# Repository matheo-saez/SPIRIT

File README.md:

<p align="center">
    
    <br>

</p>

Open source smartphone, from available components. Prioritizing user experience, performance, control, repairability, innovation and privacy.
Contribution and feedback are very welcome! [Contribution Guide](https://github.com/V3lectronics/SPIRIT/blob/main/CONTRIBUTING.md).
(Currently in the development phase, progress documented here and on the V Electronics [YT channel](https://www.youtube.com/@V_Electronics)).

> [!WARNING]
> For imformation about the project please refer to the **[wiki](https://github.com/V3lectronics/SPIRIT/wiki)**, the contents below may be outdated.
> Soon all information will be moved to the wiki!

# Contents
1. [General Specifications](https://github.com/barbarjan/SPIRIT#general-specifications)
2. [Hardware And Electronics](https://github.com/barbarjan/SPIRIT#hardware-and-electronics)
3. [Software And Operating System](https://github.com/barbarjan/SPIRIT#software-and-operating-system)
4. [DIY Build Guide](https://github.com/barbarjan/SPIRIT#diy-build-guide)
5. [Parts List](https://github.com/barbarjan/SPIRIT#parts-list)
6. [Cost](https://github.com/barbarjan/SPIRIT#cost)
7. [Ethical And Environmental Concerns](https://github.com/barbarjan/SPIRIT#ethical-and-environmental-concerns)
8. [Compliance And Legality](https://github.com/barbarjan/SPIRIT#compliance-and-legality)
9. [Resources](https://github.com/barbarjan/SPIRIT#resources)

---

Early screenshots:

# General Specifications

#### RAM

- 2GB / 4GB / 8GB / 16GB LPDDR4

#### CPU

- Broadcom BCM2712 64-bit 2.4 GHz, 4 cores with 4 threads

#### Storage

- 16GB, 32GB, or 64GB eMMC

#### Connectivity (IO)

- 1 x USB C 3.2 (Iphone 16 is USB 2.0 just throwing that out there)
- 2.4 GHz, 5.0 GHz WiFi
- Bluetooth 5
- GSM
- GPS

#### Screen

- 5.5" Capacitive Touch TFT Display
- resolution: 720x1280 pixels

#### Battery

_will probably change soon because of component availability_
- Capacity: 2.05Ah
- Type: Lithium Polymer
- Voltage: 3.7 V
- Dimensions: 84.5mm x 47.5mm x 6.0mm (3.33" 1.87" 0.24")
- The battery can be easily swapped for a fully charged one to effectively get back to 100%
almost instantly.

#### Dimensions

Chassis: ?

PCB: 80mm x 150mm

Total: thickness is ~12.3mm (excluding camera module lens sticking out)

Main components that contribute thickness:

| Component      | Thickness |
|----------------|-----------|
| Chassis        | 1 mm      |
| PCB            | 1.4 mm    |
| Battery        | 6 mm      |
| Screen         | 3.9 mm    |

#### Camera

SPIRIT is compatible with [Arducam](https://www.arducam.com/) cameras e.g. the [64 MP Hawkeye](https://www.arducam.com/64mp-ultra-high-res-camera-raspberry-pi/) or the more affordable [16 MP Autofocus](https://www.arducam.com/16mp-autofocus-camera-for-raspberry-pi/).

The camera module can be completely powered off by the user using a physical switch.

Below are the stats for the Hawkeye:

| Name    | Sensor Resolution  | Zoom | Field Of View |
|---------|-----------------|-----|---------------|
|Pi Hawk-eye| 64MP (9152 x 6944 pixels) |  10x (digital) | 84 degrees |

Sensor: 1/1.7" stacked CMOS image sensor, 0.8 μm pixel size Lens: f/1.8 aperture, 8 cm–∞ focal range, motorised focusing Max Resolution: 9152×6944 stills; 1080p 30 fps video

For more details see the [product page](https://www.arducam.com/64mp-ultra-high-res-camera-raspberry-pi/)

*(For now there is only one camera for simplicity and cost reduction)*

# Hardware And Electronics

### Raspberry Pi Compute Module 5

"The power of Raspberry Pi 5 in a compact form factor for deeply embedded applications" [(CM5 website)](https://www.raspberrypi.com/products/compute-module-5/?variant=cm5-104032).

By default SPIRIT uses the 4GB RAM, 64GB eMMC version of the CM. It is possible to use a different CM5 variant (for example to increase the RAM to 8GB).

### EDA

For schematics, PCB layout etc. the newest major release of KiCad is used.

All EDA files are available through this repository (see the 'EDA-kicad' folder). The best way to view them is to clone the repo to your machine and use KiCad to open the project file 'cm5-carrier.kicad_pro'.

### Carrier PCB

Custom carrier board (motherboard) that interfaces between the Compute Module and the rest of the electronics.

This is the only custom electronic component in this project.

### Touchscreen

Capacitive LCD Display TFT MIPI 
Dimensions: 5.5" (139.70mm) 1280px x 720px

### Replaceable Battery

Can be completely disconnected by the user using a physical switch.

The battery is mounted such that it can be easily uninstalled for replacing or privacy reasons. The user is free to swap the battery for any compatible model.
It is also possible to run the phone without a battery, or using an external one
if you attach long enough wires.

An added benefit is that the user can easily replace an empty battery for a charged one - effectively eliminating the need to wait for the phone to charge. An external battery charger can also be used for unmounted batteries.

### GSM, GPS Module

EC25VFA-512-STD

Can be completely powered off by the user using a physical switch.
Cellular, Navigation BeiDou, EDGE, Galileo, GLONASS, GPS, GNSS, LTE Transceiver Module 1.561GHz, 1.575GHz, 1.602GHz

### Speakers

2 x CMR-15062S-67

The speaker system consists of a pair of speakers mounted symmetrically facing upwards.

### Biometric Module

100018754

The fingerprint scanner is located on the back of the phone and has a sensing
area of 8x8mm. It is rated for 10 million finger placements and can store up to
50 templates.

False acceptance rate: 1/500k (per finger)
False rejection rate: 1.4-3.5 %

### Headphone Jack

This phone has a TRRS headphone jack. This way the user can decide between wireless or wired.

### Microphone

SPH0645LM4H-B

Can be completely powered off by the user using a physical switch.
Omnidirectional with a theorethical frequency range 20 Hz - 10 kHz.
Sensitivity: -26dB ±3dB @ 94dB SPL.
Digital output (I2S)

### Buttons

The power, volume and programmable buttons are identical rectangular, tactile switches with a life
expectancy of 30k cycles.

The Programmable Button's function can be customized by the user. For example, it can be used for quick launching an app, instantly dialing a saved contact, toggling sound settings (silent, vibrate, sound) etc. The list of potential use cases is very long. One of them could be enabling small children or elderly people to instantly call for example a parent, or supervisor in case of emergency. Another could be to immediately launch the camera app to quickly capture a moment.

### Privacy Switches

SPIRIT has 4 physical switches that cut off the power lines to specific modules
ensuring they are 100% inactive and not drawing power. Notice, you can also
completely disconnect the battery. Needless to say, this is a very useful
feature for people who want to have direct control over the hardware and want to
protect their privacy without having to trust software.

| Switch Number | Module |
|----------------|-----------|
| 1| Microphone|
| 2|GPS/GSM EC25 chip |
| 3|Camera |
| 4|Battery |

### Flashlight

LXML-PWC1-0100

1W 3V white, cool LED.

Toggling on/off can be binded to the programmable button.

# Software And Operating System

Once the hardware platform is functional it will be time to test various operating
systems as well as explore the possibility of developing one based on Debian.

List of operating systems to test/research:

| Name           | Website |
|----------------|-----------|
| Ubuntu Touch   | https://ubuntu-touch.io/     |
| Lineage        | https://lineageos.org/    |
| Graphene       | https://grapheneos.org/features      |
| Android        | https://www.android.com/      |

Additionally, The Yocto Project has been suggested (not an OS) https://www.yoctoproject.org/

# DIY Build Guide

Link to build guide/tutorial: COMING SOON!!!

# Parts List

The list is incomplete and old, it will be updated as soon as we have built the 1st prototype

To get the most up-to-date parts list please look
at the BOM. Certain components such as the camera or the compute module can be swapped for a different
model - the presented setup is just a suggestion.

<details>
      <summary>Click here to show/hide</summary>

| Amount | Name | Unit Price (USD)| Digikey Link |
|--------|------|---------------|--------------|
|1|RPi CM4 |65|https://www.digikey.pl/en/products/detail/raspberry-pi/SC0686/13530938?s=N4IgjCBcoLQCxVAYygMwIYBsDOBTANCAPZQDaIAHAJwAMVA7CALoC%2BLhATGSBwGxwUYAZQDCNZiyA|
|1| Carrier PCB|?|N/A|
|1| Touch screen|96,99|https://www.digikey.pl/en/products/detail/nxp-usa-inc/RK055HDMIPI4MA0/16274141 |
|1| Main Camera|66|https://www.digikey.com/en/products/detail/sparkfun-electronics/SEN-21276/21443092 |
|1| Battery|9,85|https://www.digikey.pl/en/products/detail/jauch-quartz/LP504783JU-PCM-2-WIRES-70MM/13540155|
|1| ??? BMS chip | | |
|1| 21 pin FFC connector|2.76|https://www.digikey.ca/en/products/detail/hirose-electric-co-ltd/FH72-31S-0-3SHW/13553267|
|1| 22 pin FFC connector|2,21|https://www.digikey.pl/en/products/detail/hirose-electric-co-ltd/FH12-22S-0-5SH-55/1110321|
|1| 10 pin FFC connector|0,20|https://www.digikey.pl/en/products/detail/te-connectivity-amp-connectors/1-2328702-0/9565577|
|1| Flashlight LED|3,03|https://www.digikey.pl/en/products/detail/lumileds/LXML-PWC1-0100/3961144|
|1| 35mm Jack|0.97|https://www.digikey.com/en/products/detail/same-sky-formerly-cui-devices/SJ2-3574A-SMT-TR/6619530|
|2| Speaker|2,53|https://www.digikey.pl/en/products/detail/cui-devices/CMR-15062S-67/9561156|
|1| Microphone|1,95|https://www.digikey.pl/en/products/detail/knowles/SPH0645LM4H-B/5332440|
|1| USB C 2.0 Connector|0,81|https://www.digikey.com/en/products/detail/gct/USB4105-GF-A/11198441|
|?| Overvoltage protector|0,43|https://www.digikey.pl/en/products/detail/littelfuse-inc/SMBJ5-0A/285950|
|1| Fingerprint Card|29|https://www.digikey.pl/en/products/detail/fingerprint-cards-ab/100018754/11480144?s=N4IgjCBcpgnAHLKoDGUBmBDANgZwKYA0IA9lANogAMIAugL7EC0ATMiGpAC4BOArkVIUQAVjqMQTAGztOvAcTKRKAZhDE2DCW2Uh0ASwB2Ac3w8ADjyNdxQA|
|1| GPS Module|7,25|https://www.digikey.pl/en/products/detail/yic/YIC31009EBGG/16499057|
|1| GSM Module|||
|1| Vibration Motor|1,71|https://www.digikey.pl/en/products/detail/pui-audio-inc/HD-EMB1205-3-SC-R/16522073|
|1| Small LED|||
|1| Thermistor|0,10|https://www.digikey.pl/en/products/detail/panasonic-electronic-components/ERT-JZEG103FA/9646736|
|1| DAC for audio output||
|1| Jumper female nRPI_BOOT||
|1| Jumper female GND||
|?| Header pins||
|?| M1.6 stainless screws||
|?| M? RPi size stainless screws||
|?| M? Arducam size stainless screws||
|?| M? RPi size stainless tandoffs||

</details>

# Cost

The total assembly cost of the device is unknown

# Ethical And Environmental Concerns

SPIRIT phones avoid components produced in unfair or harmful ways, as well as
containing conflict minerals if possible.

TODO
Here are ethical details for each major component:

-Chassis
-CM5
-Battery
-Screen
-Chassis
-Speakers

The goal is to be 100% ethically and environmentally "clean" as soon as possible, however that is
a hard task and presents multiple enginnering challenges.

TODO
?RoHS complicance

# Compliance And Legality

TODO research

### EU

Ecodesign Regulation 2023/1670

?EMI norms

?RoHS

?REACH

?WEEE

### N America
?

### S America
?

### Asia
?

### Africa
?

### Australia
?

# Resources

- [Rpi CM5 datasheet](https://datasheets.raspberrypi.com/cm5/cm5-datasheet.pdf)
- [Rpi CM4 pinout from datasheet](https://datasheets.raspberrypi.com/cm4/cm4-datasheet.pdf#page=18)
- [Rpi CM5 and CM 4 very useful interactive pinout](https://atctwo.net/projects/pinout/index.html)

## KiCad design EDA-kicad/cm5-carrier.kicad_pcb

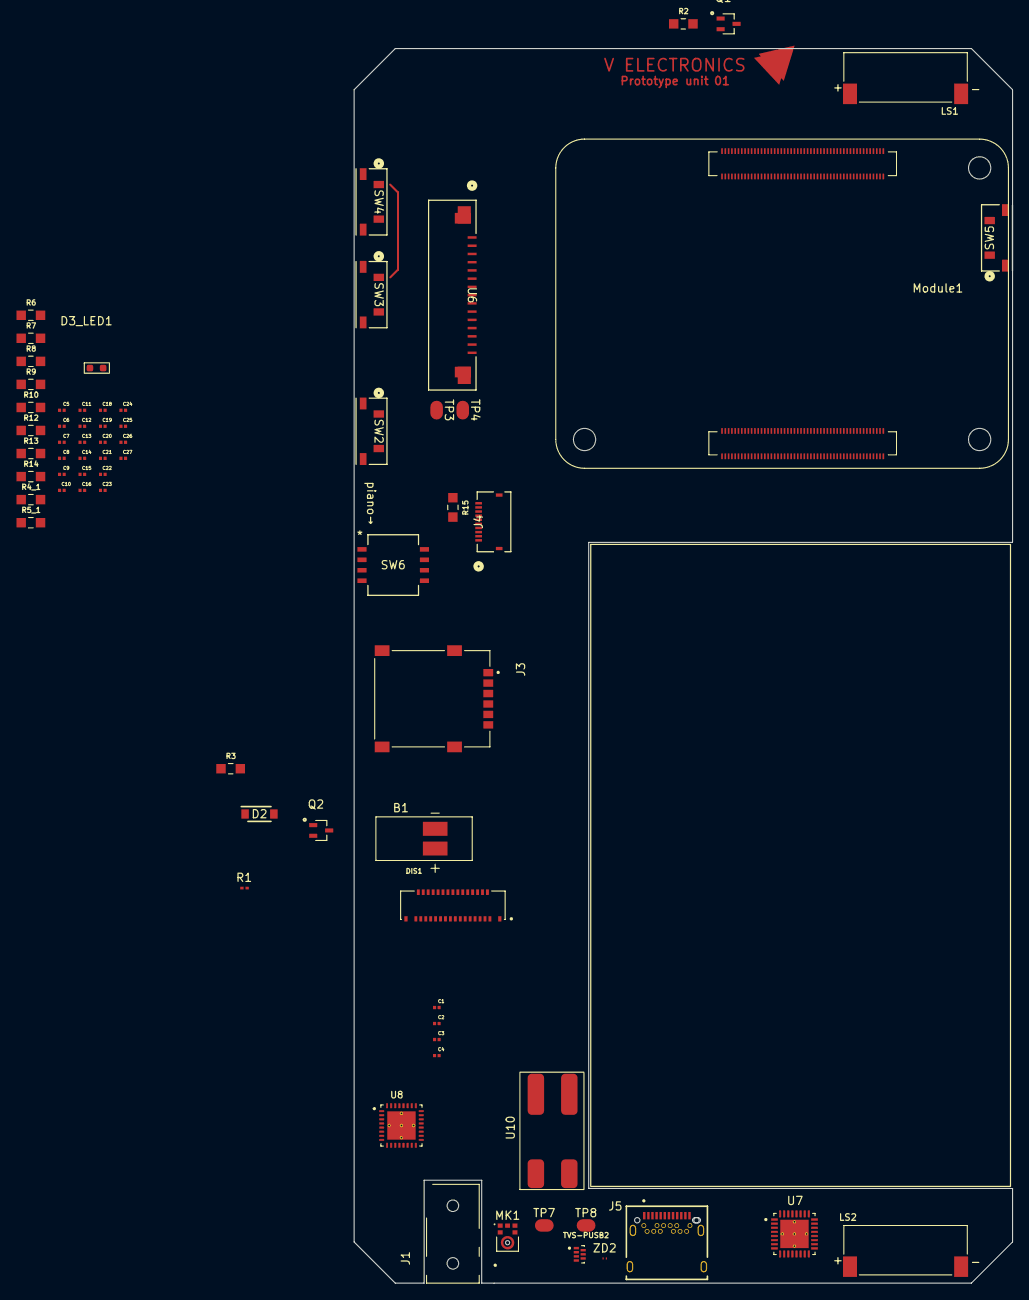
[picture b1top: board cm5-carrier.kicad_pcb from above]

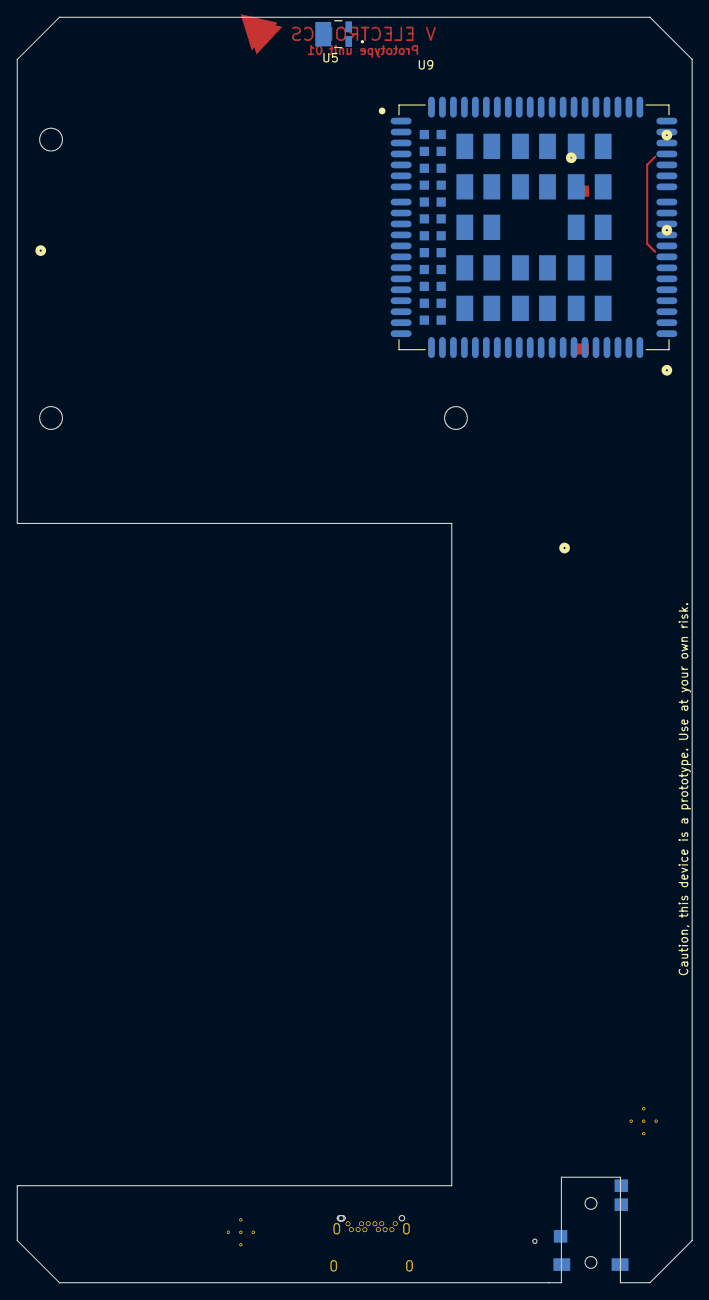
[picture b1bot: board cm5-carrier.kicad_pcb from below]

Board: 2 copper layers, 80.0 x 150.0 mm, 72 parts (2 on the bottom side), 63 nets.

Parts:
B1: VIBR; VIBRATION-PUI_HD-EMB1205-3-SC-R
BAT2: battery_37V3500mAhLP685077JU
C1, C2, C3, C4: 0.33 µF coupling cap; USBC_capacitor_CAPC0603X33N
C5, C11, C21, C24, C27: 0.1μF; USBC_capacitor_CAPC0603X33N
C6, C7, C8, C9, C10, C12, C13, C14, C15, C16, C22, C23: 10μF; USBC_capacitor_CAPC0603X33N
C18, C19: 47nF; USBC_capacitor_CAPC0603X33N
C20: 4.7μF; USBC_capacitor_CAPC0603X33N
C25, C26: 2.2μF; USBC_capacitor_CAPC0603X33N
D2: 1N4007W-T; flyback-diode-SODFL3818X130N
D3_LED1: LED-INDICATOR
DIS1: FH72-31S-0.3SHW; HRS_FH72-31S-0.3SHW
J1: SJ2-35894B-SMT-TR; 35mmJACK-CUI_SJ2-35894B-SMT-TR
J3: SIM-G85D1160022HHR; SIM-AMPHENOL_G85D1160022HHR
J4: FINGER; 10PIN
J5: USBC-3-2-fix-USB4056-03-A_REVA2; USBC-3-2-fix-GCT_USB4056-03-A_REVA2
LS1, LS2: CMR-15062S-67; SPEAKER_CMR-15062S-67
MK1: microphone; microphone_SPH0645LM4H-B
Module1: ComputeModule5-CM5; Raspberry-Pi-5-Compute-Module
Q1, Q2: gpio-driver-transistor-fix-SOT65P210X110-3N
R1: thermistor; thermistor-NTC0201Z_P63XP33_PAN
R2, R3: 1K-05W-0805-RES_ERJP06J102V
R4_1: 6.04k; 1K-05W-0805-RES_ERJP06J102V
R5_1: 100k; 1K-05W-0805-RES_ERJP06J102V
R6: 5.24k; 1K-05W-0805-RES_ERJP06J102V
R7: 30.31k; 1K-05W-0805-RES_ERJP06J102V
R8: 10k; 1K-05W-0805-RES_ERJP06J102V
R9: 100; 1K-05W-0805-RES_ERJP06J102V
R10, R12: R; 1K-05W-0805-RES_ERJP06J102V
R13, R14: 2; 1K-05W-0805-RES_ERJP06J102V
R15: 270K-05W-0805-RES_ERJP06J102V; 1K-05W-0805-RES_ERJP06J102V
SW2: PROG; buttonSW_TL3330_EWI
SW3: VOL-; buttonSW_TL3330_EWI
SW4: VOL+; buttonSW_TL3330_EWI
SW5: POW; buttonSW_TL3330_EWI
SW6: CHP-041B; pianoCHP-041B_NDC
TP3, TP4, TP7, TP8: test-pad-1
TVS-PUSB2: TVS-array-IC_PUSB3AB6Z
U5: Flash-LED-Lumiled; LUMILED-DIODFN449X305X210-3N
U6: FPC15pin-1mm-pitch-F52Q-1A7H1-11015; FPC15pin-1mm-pitch-CONN_F52Q-1A7H1-11015_AMP
U7: CODEC-TLV320AIC3204IRHBR; CODEC-QFN50P500X500X100-33N
U8: DAC-TLV320DAC3100IRHBR; DAC-IC_ADS125H01IRHBT
U9: GSM-GPS-EC25VFA-512-STD; GSM-GPS-XCVR_EC25VFA-512-STD
U10: BAT-CONNECTOR-FLTS22WR00
ZD2: protection-PESD5V0C1USFYL; USB-ESD-protection-diode-PESD5V0C1USFYL-SOD962-2_DSN0603-2_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

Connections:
BAT: C15.1, C16.1
CAM-SWITCH: SW6.6, TP3.1 (A), U6.15
CAM_CK_N: Module1.127 (MIPI0_C_N), U6.8
CAM_CK_P: Module1.129 (MIPI0_C_P), U6.9
CAM_D0_N: Module1.115 (MIPI0_D0_N), U6.2
CAM_D0_P: Module1.117 (MIPI0_D0_P), U6.3
CAM_D1_N: Module1.121 (MIPI0_D1_N), U6.5
CAM_D1_P: Module1.123 (MIPI0_D1_P), U6.6
CAM_IO0: TP4.1 (A), U6.11
CC1: J5.A5 (CC1), Module1.94 (CC1)
CC2: J5.B5 (CC2), Module1.96 (CC2)
CODEC SCL: Module1.51 (GPIO15), U7.9 (SCL/~SS)
CODEC SDA: Module1.31 (GPIO12), U7.10 (SDA/MOSI)
D+: J5.A6 (DP1), J5.B6 (DP2), Module1.163 (USB3-1-D_P), TVS-PUSB2.5 (D+)
D-: J5.A7 (DN1), J5.B7 (DN2), Module1.165 (USB3-1-D_N), TVS-PUSB2.4 (D-)
DIS SCL: DIS1.27, Module1.37 (GPIO7)
DIS SDA: DIS1.26, Module1.30 (GPIO6)
DSI1_C_N: DIS1.11, Module1.187 (MIPI1_C_N)
DSI1_C_P: DIS1.12, Module1.189 (MIPI1_C_P)
DSI1_D0_N: DIS1.5, Module1.175 (MIPI1_D0_N)
DSI1_D0_P: DIS1.6, Module1.177 (MIPI1_D0_P)
DSI1_D1_N: DIS1.8, Module1.181 (MIPI1_D1_N)
DSI1_D1_P: DIS1.9, Module1.183 (MIPI1_D1_P)
DSI1_D2_N: DIS1.14, Module1.133 (MIPI0_D2_N), Module1.193 (MIPI1_D2_N)
DSI1_D2_P: DIS1.15, Module1.135 (MIPI0_D2_P), Module1.195 (MIPI1_D2_P)
GND: C5.2, C6.2, C7.2, C8.2, C9.2, C10.2, C11.2, C12.2, C13.2, C14.2, C15.2, C16.2, C20.2, C21.2, C22.2, C23.2, C24.2, C25.2, C26.2, C27.2, DIS1.1, DIS1.4, DIS1.7, DIS1.10, DIS1.13, DIS1.16, DIS1.19, DIS1.20, DIS1.31, J3.C5 (GND), J3.S1 (SHIELD_GND), J3.S2 (SHIELD_GND__1), J3.S3 (SHIELD_GND__2), J4.1, J5.A1 (GND_A), J5.A12 (GND_A__1), J5.B1 (GND_B), J5.B12 (GND_B__1), J5.S1 (SHELL_GND), J5.S2 (SHELL_GND__1), J5.S3 (SHELL_GND__2), J5.S4 (SHELL_GND__3), MK1.3 (GND), Module1.1 (GND), Module1.2 (GND), Module1.8 (GND), Module1.13 (GND), Module1.14 (GND), Module1.22 (GND), Module1.23 (GND), Module1.32 (GND), Module1.33 (GND), Module1.42 (GND), Module1.43 (GND), Module1.52 (GND), Module1.53 (GND), Module1.60 (GND), Module1.66 (GND), Module1.71 (GND), Module1.74 (GND), Module1.98 (GND), Module1.107 (GND), Module1.108 (GND), Module1.113 (GND), Module1.114 (GND), Module1.119 (GND), Module1.120 (GND), Module1.125 (GND), Module1.126 (GND), Module1.131 (GND), Module1.132 (GND), Module1.137 (GND), Module1.138 (GND), Module1.144 (GND), Module1.150 (GND), Module1.155 (GND), Module1.156 (GND), Module1.161 (GND), Module1.162 (GND), Module1.167 (GND), Module1.168 (GND), Module1.173 (GND), Module1.174 (GND), Module1.179 (GND), Module1.180 (GND), Module1.185 (GND), Module1.186 (GND), Module1.191 (GND), Module1.192 (GND), Module1.197 (GND), Module1.198 (GND), Q1.3 (S), Q2.3 (S), R4_1.1, R5_1.2, R7.2, R8.2, TVS-PUSB2.2 (GND), U6.1, U6.4, U6.10, U7.7 (IOVSS), U7.17 (AVSS), U7.28 (DVSS), U8.1 (IOVSS), U8.16 (AVSS), U8.18 (DVSS), U8.20 (SPKVSS), U8.25 (SPKVSS__1), U8.29 (HPVSS), U9.8 (GND), U9.9 (GND__1), U9.19 (GND__2), U9.22 (GND__3), U9.36 (GND__4), U9.46 (GND__5), U9.48 (GND__6), U9.50 (GND__7), U9.51 (GND__8), U9.52 (GND__9), U9.53 (GND__10), U9.54 (GND__11), U9.56 (GND__12), U9.72 (GND__13), U9.85 (GND__14), U9.86 (GND__15), U9.87 (GND__16), U9.88 (GND__17), U9.89 (GND__18), U9.90 (GND__19), U9.91 (GND__20), U9.92 (GND__21), U9.93 (GND__22), U9.94 (GND__23), U9.95 (GND__24), U9.96 (GND__25), U9.97 (GND__26), U9.98 (GND__27), U9.99 (GND__28), U9.100 (GND__29), U9.101 (GND__30), U9.102 (GND__31), U9.103 (GND__32), U9.104 (GND__33), U9.105 (GND__34), U9.106 (GND__35), U9.107 (GND__36), U9.108 (GND__37), U9.109 (GND__38), U9.110 (GND__39), U9.111 (GND__40), U9.112 (GND__41), U10.4 (OUT-), ZD2.2
GPIO2: Module1.58 (GPIO2), SW5.2
GPIO3: Module1.56 (GPIO3), SW4.2
GPIO4: Module1.54 (GPIO4), SW3.2
GPIO17: Module1.50 (GPIO17), SW2.2
GPIO22: Module1.46 (GPIO22), R2.1
GPIO27: Module1.48 (GPIO27), R3.1
MIC-SWITCH: MK1.5 (VDD), SW6.8
unnamed: C25.1, R13.1
unnamed: C26.1, R14.1
unnamed: J4.8, R15.2
unnamed: C1.1, Module1.157 (USB3-1-RX_N)
unnamed: C2.1, Module1.159 (USB3-1-RX_P)
unnamed: C3.1, Module1.169 (USB3-1-TX_N)
unnamed: C4.1, Module1.171 (USB3-1-TX_P)
unnamed: Q1.2 (D), U5.1 (-)
unnamed: Q1.1 (G), R2.2
unnamed: B1.N, D2.2, Q2.2 (D)
unnamed: Q2.1 (G), R3.2
unnamed: C11.1, C12.1, C13.1, C14.1
unnamed: R6.2, R7.1, R8.1
OUT +: R9.2, U10.3 (OUT+)
REGN: C18.2, C19.1, C20.1, R6.1
RX1+: C2.2, J5.A11 (SSRXP2), J5.B11 (SSRXP1), TVS-PUSB2.7 (RX+)
RX1-: C1.2, J5.A10 (SSRXN2), J5.B10 (SSRXN1), TVS-PUSB2.6 (Rx-)
SPI0_CLK: J4.2, Module1.38 (GPIO11)
SPI0_CS: J4.5, Module1.39 (GPIO8)
SPI0_MISO: J4.3, Module1.40 (GPIO9)
SPI0_MOSI: J4.4, Module1.44 (GPIO10)
SPI0_RDY: J4.6, Module1.34 (GPIO5)
SYS: C5.1, C6.1, C7.1, C8.1, C9.1, C10.1
TX1+: C4.2, J5.A2 (SSTXP1), J5.B2 (SSTXP2), TVS-PUSB2.3 (Tx+)
TX1-: C3.2, J5.A3 (SSTXN1), J5.B3 (SSTXN2), TVS-PUSB2.1 (Tx-)
USBC POW: J5.A4 (VBUS_A), J5.A9 (VBUS_A__1), J5.B4 (VBUS_B), J5.B9 (VBUS_B__1), ZD2.1
VAC1: C27.1, R14.2
VAC2: C24.1, R13.2
VBUS: C21.1, C22.1, C23.1, R10.1
VCC: B1.P, D2.1, DIS1.25, DIS1.30, J4.7, J4.10, R15.1, SW2.1, SW3.1, SW4.1, SW5.1, SW6.1, SW6.2, SW6.3, U5.2 (+), U7.24 (AVDD), U8.2 (IOVDD), U8.3 (DVDD), U8.17 (AVDD), U8.21 (SPKVDD), U8.24 (SPKVDD__1)

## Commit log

2025-08-13 fix speaker clearance issue
2025-08-13 typo
2025-08-13 last adjustement
